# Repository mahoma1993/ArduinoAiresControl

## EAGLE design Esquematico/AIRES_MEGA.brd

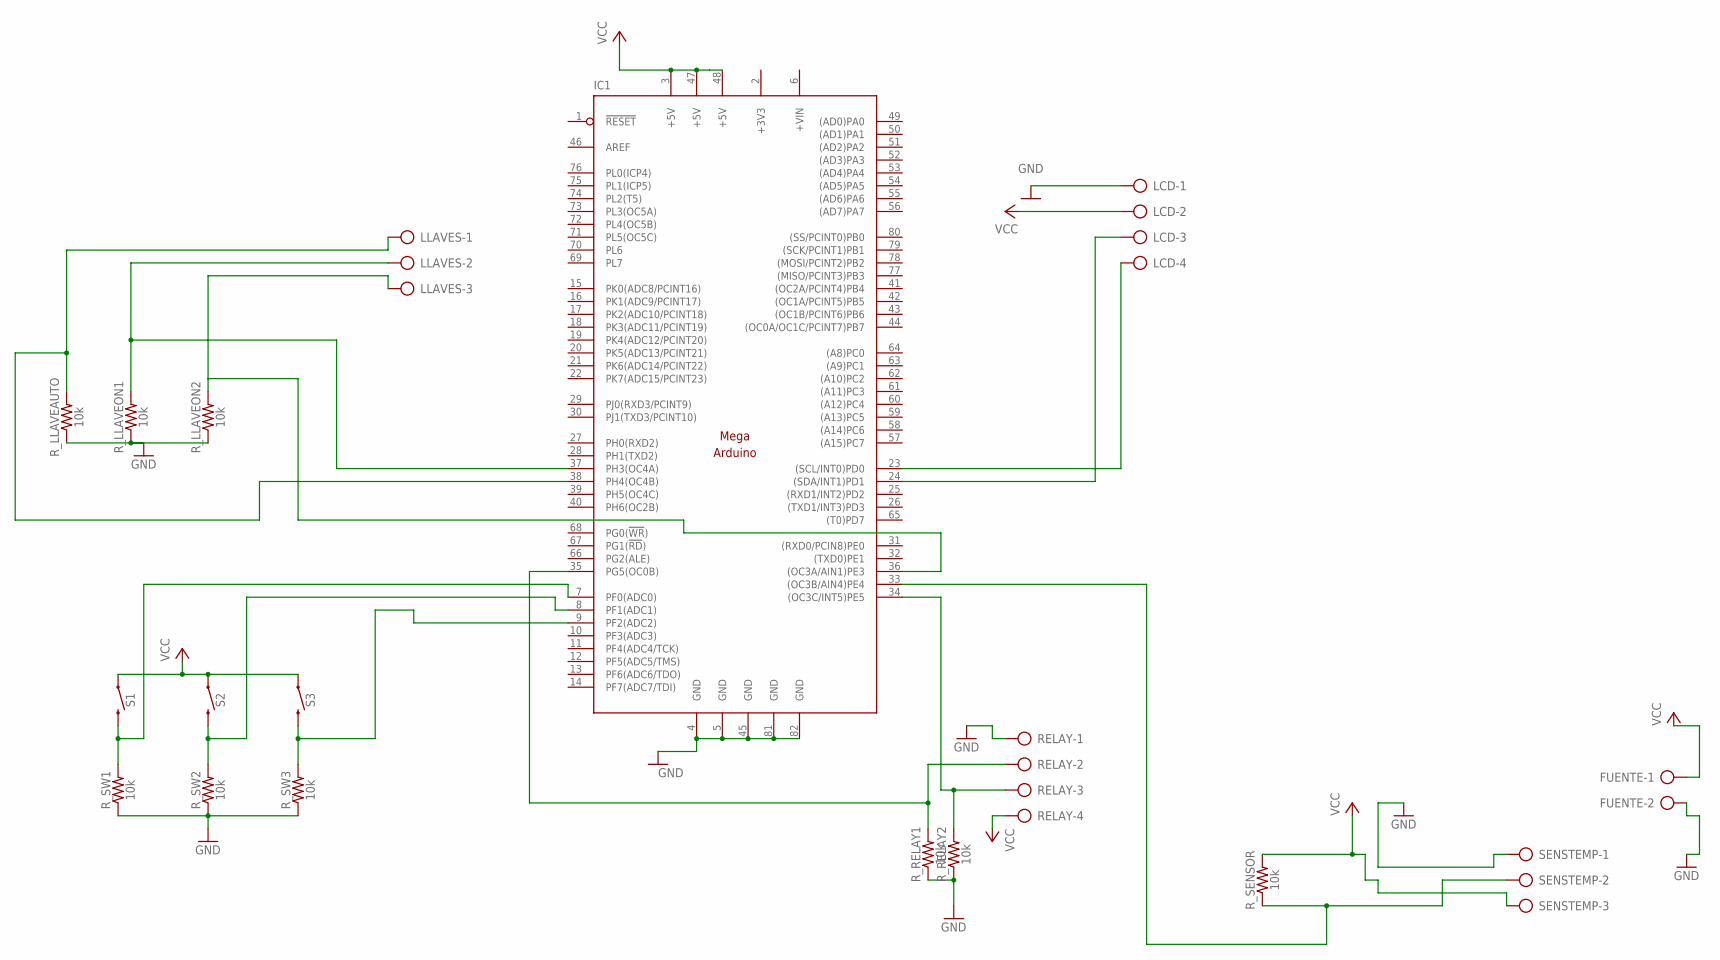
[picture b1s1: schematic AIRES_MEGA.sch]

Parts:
FUENTE: AK500/2
IC1: MEGAARDUINO_1; MEGA_ARDUINO
LCD: AK500/4
LLAVES: AK500/3
RELAY: AK500/4
R_LLAVEAUTO: 10k; AXIAL-0.3
R_LLAVEON1, R_LLAVEON2: 10k; AXIAL-0.3
R_RELAY1, R_RELAY2: 10k; AXIAL-0.3
R_SENSOR: 10k; AXIAL-0.3
R_SW1, R_SW2, R_SW3: 10k; AXIAL-0.3
S1, S2, S3: MOMENTARY-SWITCH-SPST-PTH-12MM; TACTILE_SWITCH_PTH_12MM
SENSTEMP: AK500/3

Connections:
+3V3: IC1.2 (+3V3)
+VIN: IC1.6 (+VIN)
GND: FUENTE.2, IC1.4 (GND), IC1.5 (GND), IC1.45 (GND), IC1.81 (GND), IC1.82 (GND), LCD.1, RELAY.1, R_LLAVEAUTO.P$1 (1), R_LLAVEON1.P$1 (1), R_LLAVEON2.P$1 (1), R_RELAY1.P$1 (1), R_RELAY2.P$1 (1), R_SW1.P$1 (1), R_SW2.P$1 (1), R_SW3.P$1 (1), SENSTEMP.1
unnamed: IC1.24 ((SDA/INT1)PD1), LCD.3
unnamed: IC1.35 (PG5(OC0B)), RELAY.2, R_RELAY1.P$2 (2)
unnamed: IC1.38 (PH4(OC4B)), LLAVES.1, R_LLAVEAUTO.P$2 (2)
unnamed: IC1.7 (PF0(ADC0)), R_SW1.P$2 (2), S1.3 (2)
unnamed: IC1.37 (PH3(OC4A)), LLAVES.2, R_LLAVEON1.P$2 (2)
unnamed: IC1.8 (PF1(ADC1)), R_SW2.P$2 (2), S2.3 (2)
unnamed: IC1.23 ((SCL/INT0)PD0), LCD.4
unnamed: IC1.34 ((OC3C/INT5)PE5), RELAY.3, R_RELAY2.P$2 (2)
unnamed: IC1.9 (PF2(ADC2)), R_SW3.P$2 (2), S3.3 (2)
unnamed: IC1.36 ((OC3A/AIN1)PE3), LLAVES.3, R_LLAVEON2.P$2 (2)
PIN_SENSOR: IC1.33 ((OC3B/AIN4)PE4), R_SENSOR.P$1 (1), SENSTEMP.2
VCC: FUENTE.1, IC1.3 (+5V), IC1.47 (+5V), IC1.48 (+5V), LCD.2, RELAY.4, R_SENSOR.P$2 (2), S1.1, S2.1, S3.1, SENSTEMP.3

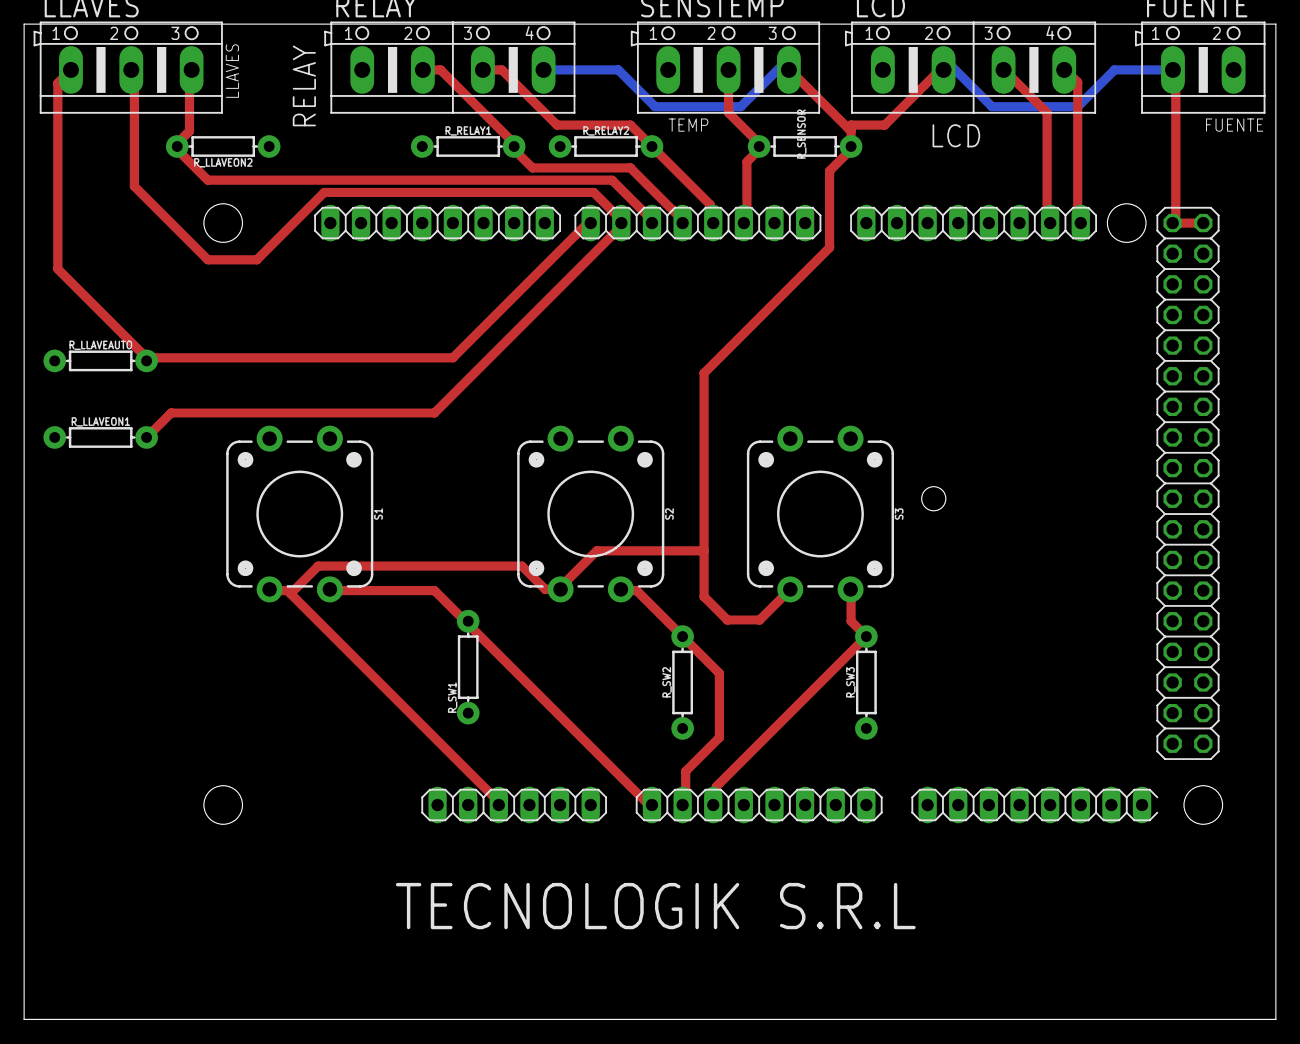
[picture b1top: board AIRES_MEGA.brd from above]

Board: 2 copper layers, 103.8 x 82.5 mm, 18 parts (0 on the bottom side), 13 nets.

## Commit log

2022-11-18 Version Final

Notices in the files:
parts and their libraries:
SparkFun-Resistors: Licensing: Creative Commons ShareAlike 4.0 International - https://creativecommons.org/licenses/by-sa/4.0
